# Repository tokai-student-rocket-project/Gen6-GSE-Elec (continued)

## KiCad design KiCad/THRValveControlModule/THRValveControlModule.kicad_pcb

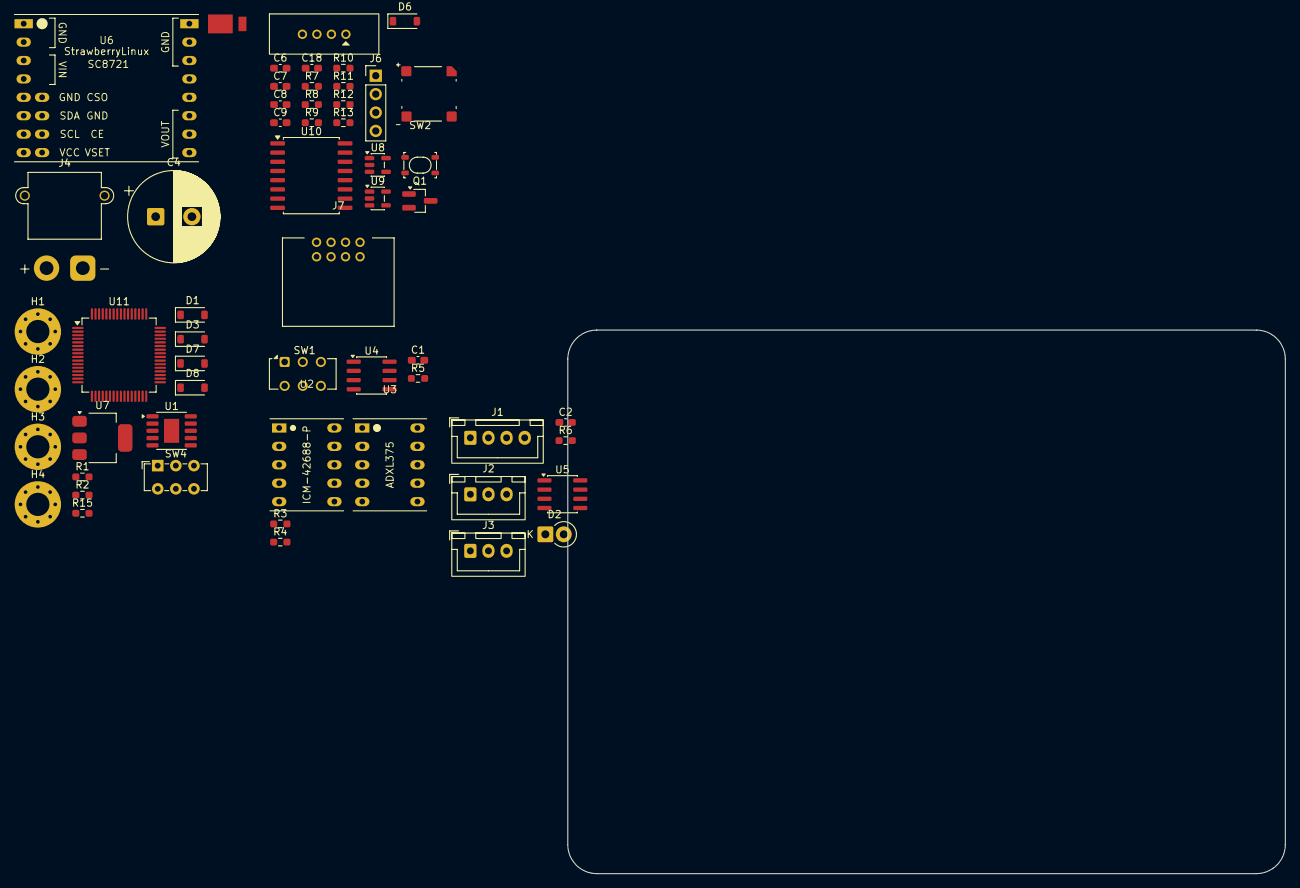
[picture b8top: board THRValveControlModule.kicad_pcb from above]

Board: 2 copper layers, 99.0 x 75.0 mm, 56 parts (0 on the bottom side), 29 nets, no tracks yet.

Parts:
C1, C2, C6, C7, C8, C9: 0.1u; C_0603_1608Metric_Pad1.08x0.95mm_HandSolder
C4: 1000u; CP_Radial_D12.5mm_P5.00mm
C18: 0.1uF; C_0603_1608Metric_Pad1.08x0.95mm_HandSolder
D1, D3, D7, D8: RB160M-30TR; D_SOD-123
D2: P4KE15A; D_DO-41_SOD81_P2.54mm_Vertical_KathodeUp
D5: MA10EB045; MA_DO-221BC
D6: 1N4148W; D_SOD-123
H1, H2, H3, H4: MountingHole; MountingHole_3.2mm_M3_Pad_Via
J1: B4B-XH-A(LF)(SN); JST_XH_B4B-XH-A_1x04_P2.50mm_Vertical
J2, J3: B3B-XH-A(LF)(SN); JST_XH_B3B-XH-A_1x03_P2.50mm_Vertical
J4: XT30PW-M; AMASS_XT30PW-M_1x02_P2.50mm_Horizontal
J5: DF51A-4P-2DSA
J6: SSD1306; PinHeader_1x04_P2.54mm_Vertical
J7: DF51A-8DP-2DS
LS1: UGCT7525AN4
Q1: IRLML6344TRPBFTR; SOT-23_Handsoldering
R1, R2, R7, R8, R10, R11, R12, R13, R15: 10k; R_0603_1608Metric_Pad0.98x0.95mm_HandSolder
R3, R4: 4.7k; R_0603_1608Metric_Pad0.98x0.95mm_HandSolder
R5, R6: 120; R_0603_1608Metric_Pad0.98x0.95mm_HandSolder
R9: 1k; R_0603_1608Metric_Pad0.98x0.95mm_HandSolder
SW1: IS-2235; SW_CK_JS202011CQN_DPDT_Straight
SW2: SKRPACE010
SW4: SW_DPDT_x2; SW_E-Switch_EG1271_SPDT
U1: CH340K; SSOP-10-1EP_3.9x4.9mm_P1mm_EP2.1x3.3mm
U2: ICM-42688; StrawberryLinux_ICM-42688-P
U3: ADXL375; StrawberryLinux_ADXL375
U4: ATA6561; SOIC-8_3.9x4.9mm_P1.27mm
U5: MAX485E; SOIC-8_3.9x4.9mm_P1.27mm
U6: SC8721; StrawberryLinux_SC8721
U7: AZ1117CH-3.3TRG1; SOT-223-3_TabPin2
U8, U9: TC7S14F; SOT-23-5
U10: MB85RQ8MX; SOIC-16W_7.5x10.3mm_P1.27mm
U11: STM32F446RETx; LQFP-64_10x10mm_P0.5mm

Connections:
+3.3V: C7.1, C9.1, C18.1, D3.2 (A), J6.2, R1.1, R2.1, R3.1, R4.1, R7.2, R11.2, R13.1, R15.1, SW4.1 (A), U1.7 (VCC), U1.10 (V3), U2.1 (VDD), U2.2 (VDDIO), U3.9 (VS), U3.10 (VDDI/O), U7.3 (OUT), U8.5 (VCC), U9.5 (VCC), U10.1 (~HOLD(IO3)), U10.2 (VDD), U10.9 (~WP(IO2)), U11.1 (VBAT), U11.13 (VDDA), U11.19 (VDD), U11.32 (VDD), U11.48 (VDD), U11.64 (VDD)
+5V: C1.2, C2.1, D1.2 (A), D6.1 (K), D7.2 (A), LS1.2, U4.3 (VDD), U4.5 (Vio), U5.8 (VCC)
BOOT0: SW4.2 (B), U11.60 (BOOT0)
CAN_H: J7.7, J7.8, R5.1, U4.7 (CANH)
CAN_L: J7.5, J7.6, SW1.1 (A), U4.6 (CANL)
GND: C1.1, C2.2, C4.2, C6.2, C7.2, C8.2, C9.2, C18.2, D2.1 (A1), J1.1, J2.1, J3.1, J4.1, J5.1, J5.3, J6.1, J7.1, J7.2, Q1.2 (S), R10.1, SW2.3 (K), SW2.4 (A), U1.3 (GND), U1.11 (GND), U2.10 (GND), U3.1 (GND), U3.8 (GND), U4.2 (VSS), U4.8 (STBY), U5.5 (GND), U6.1 (GND), U6.2 (GND), U6.5 (GND), U6.10 (GND), U6.18 (GND), U6.19 (GND), U6.20 (GND), U7.2 (GND), U8.3 (GND), U9.3 (GND), U10.10 (VSS), U11.12 (VSSA), U11.18 (VSS), U11.31 (VSS), U11.47 (VSS), U11.63 (VSS)
I2C_SCL: J6.3, R2.2, U6.7 (SCL)
I2C_SDA: J6.4, R1.2, U6.6 (SDA)
unnamed: C6.1, R8.2, U8.2
unnamed: C8.1, R12.2, U9.2
unnamed: D3.1 (K), D7.1 (K), D8.1 (K), U7.1 (IN)
unnamed: D5.2 (A), J4.2
unnamed: D6.2 (A), LS1.1, Q1.3 (D)
unnamed: J5.2, R11.1, R12.1
unnamed: J5.4, R7.1, R8.1
unnamed: Q1.1 (G), R9.1, R10.2
unnamed: R5.2, SW1.2 (B)
Periferal_SwitchA: R13.2, SW2.1, SW2.2
RS485_A: J1.3, R6.1, U5.6 (A)
RS485_B: J1.4, R6.2, U5.7 (B)
RS485_EN: U5.2 (~RE), U5.3 (DE)
SC8721_VIN: D5.1 (K), U6.3 (VIN), U6.4 (VIN)
SC8721_VOUT: C4.1, D2.2 (A2), D8.2 (A), J1.2, J2.2, J3.2, J7.3, J7.4, U6.13 (VOUT), U6.14 (VOUT), U6.15 (VOUT)
SPI_ADXL375_~CS: R4.2, U3.5 (~CS)
SPI_FeRAM0_~CS: R15.2, U10.7 (~CS)
SPI_ICM-42688_~CS: R3.2, U2.6 (~CS)
SPI_SCLK: U2.3 (SCL/SCLK), U3.2 (SCK/SCLK), U10.16 (SCK)
SPI_SDI: U2.4 (SDA/SDI), U3.3 (SDA/SDI/SDIO), U10.15 (SI(IO0))
SPI_SDO: U2.5 (AD0/SDO), U3.4 (SDO/ALT_ADDRESS), U10.8 (SO(IO1))

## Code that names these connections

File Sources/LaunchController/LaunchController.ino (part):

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

namespace power {
  Input killButton(PIN_PJ1, false);
  Output loadSwitch(PIN_PF5);
  Output powerLamp(PIN_PG5);
  Output lowVoltageLamp(PIN_PK7);

  PowerMonitor input(0x40);
  PowerMonitor bus12(0x41);
  Thermistor thermal(PIN_PF4, 10000.0);

  void measureTask();
} // namespace power

namespace control {
  SemiAutoControl safetyArmed(PIN_PC2, false, PIN_PH7);
  SemiAutoControl sequenceStart(PIN_PC3, false, PIN_PG3);
  SemiAutoControl emergencyStop(PIN_PC4, true, PIN_PG4);

  Input confirm1(PIN_PC7, false);
  Input confirm2(PIN_PC6, false);
  Input confirm3(PIN_PC5, false);

  SemiAutoControl shift(PIN_PD4, false, PIN_PH5);
  SemiAutoControl fill(PIN_PD5, false, PIN_PB0);
  SemiAutoControl dump(PIN_PG1, false, PIN_PB5);
  SemiAutoControl oxygen(PIN_PC1, false, PIN_PL4);
  SemiAutoControl igniter(PIN_PD7, false, PIN_PH4);
  SemiAutoControl open(PIN_PD6, false, PIN_PH6);
  SemiAutoControl close(PIN_PG0, false, PIN_PB4);
  SemiAutoControl purge(PIN_PC0, false, PIN_PB6);

  Output shiftFB(PIN_PE3);
  Output fillFB(PIN_PE5);
  Output dumpFB(PIN_PE7);
  Output oxygenFB(PIN_PH3);
  Output igniterFB(PIN_PE2);
  Output openFB(PIN_PE4);
  Output closeFB(PIN_PE6);
  Output purgeFB(PIN_PH2);

  Output statusLamp(PIN_PK4);
  void handleManualTask();

  const String FILL_START = "fill-start";
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} // namespace sequence

namespace n2o {
  TM1637 tm1637(PIN_PK0, PIN_PK1);
} // namespace n2o

namespace error {
  // HACK LEDだけでなく処理もする
  Output statusLamp(PIN_PK6);
} // namespace caution


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    COM_CHECK_S_TO_L
  };

  Output sendEnableControl(PIN_PA2);
  Output accessLamp(PIN_PA4);

  void enableOutput();
  void disableOutput();
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  void onPressureSyncReceived(float pressure);
  void onComCheckReceived();

  Output statusLamp(PIN_PK5);
} // namespace communication


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
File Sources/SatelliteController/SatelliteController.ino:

#include <Arduino.h>
#include <TaskManager.h>
#include <MsgPacketizer.h>
#include "TM1637.hpp"
#include "VESIM10.hpp"
#include "Input.hpp"
#include "Output.hpp"
#include "SemiAutoControl.hpp"
#include "SolenoidMonitor.hpp"
#include "PowerMonitor.hpp"
#include "Thermistor.hpp"


namespace power {
  Input killButton(PIN_PJ1, false);
  Output loadSwitch(PIN_PF5);
  Output powerLamp(PIN_PG5);
  Output lowVoltageLamp(PIN_PK7);

  PowerMonitor input(0x40);
  PowerMonitor bus12(0x41);
  Thermistor thermal(PIN_PF4, 10000.0);

  void measureTask();
} // namespace power

namespace control {
  SemiAutoControl safetyArmed(PIN_PC2, true, PIN_PH7);

  Output shift(PIN_PD4);
  Output fill(PIN_PD5);
  Output dump(PIN_PG1);
  Output oxygen(PIN_PL6);
  Output igniter(PIN_PD7);
  Output open(PIN_PD6);
  Output close(PIN_PG0);
  SemiAutoControl purge(PIN_PC0, true, PIN_PB6);
  // Output purge(PIN_PB6);
  // SemiAutoControl check(PIN_PC0, true, PIN_PB6);

  Output shiftFB(PIN_PH5);
  Output fillFB(PIN_PB0);
  Output dumpFB(PIN_PB5);
  Output oxygenFB(PIN_PL4);
  Output igniterFB(PIN_PH4);
  Output openFB(PIN_PH6);
  Output closeFB(PIN_PB4);
  Output purgeFB(PIN_PH1);

  Output statusLamp(PIN_PK4);
  void handleManualTask();

  void setChristmasTreeStart();
  void setChristmasTreeStop();
} // namespace control

namespace error {
  // HACK LEDだけでなく処理もする
  Output statusLamp(PIN_PK6);
} // namespace caution

namespace solenoid {
  SolenoidMonitor monitor(PIN_PC4);

  void measureTask();
} // namespace solenoid

namespace n2o {
  TM1637 tm1637(PIN_PK0, PIN_PK1);
  VESIM10 vesim10(PIN_PK2, 240.0, 10.0);

  float pressure_MPa = 0.0;

  void measureTask();
} // namespace n2o

namespace umbilical {
  Output flightMode(PIN_PH3);
  Output valveMode(PIN_PH2);
} // namespace umbilical

namespace communication {
  enum class Packet : uint8_t {
    CONTROL_SYNC,
    FEEDBACK_SYNC,
    PRESSURE_SYNC,
    COM_CHECK_L_TO_S,
    COM_CHECK_S_TO_L,
  };

  Output sendEnableControl(PIN_PA2);
  Output accessLamp(PIN_PA4);

  void enableOutput();
  void disableOutput();

  void sendFeedbackSync();
  void sendPressureSync();
  void sendComCheck();
  void onControlSyncReceived(uint8_t state);
  void onComCheckReceived();

  Output statusLamp(PIN_PK5);
} // namespace communication


void setup() {
  power::loadSwitch.on();
  power::powerLamp.on();


  // FT232RL (USB)
  Serial.begin(115200);

  // LTC485 (RS485)
  Serial1.begin(115200);

  // MCP3208 (ADC)
  SPI.begin();
  solenoid::monitor.setDividerResistance(5600, 3300);

  // TM1637 (7SEG)
  n2o::tm1637.initialize();

  // INA219 (Power)
  Wire.begin();
  power::input.begin();
  power::bus12.begin();

  // VESIM10 (N2O Pressure Sensor)
  n2o::vesim10.calibrateBlocking(10);


  Tasks.add(&power::measureTask)->startFps(10);
  Tasks.add(&solenoid::measureTask)->startFps(10);
  Tasks.add(&n2o::measureTask)->startFps(2);
  Tasks.add(&control::handleManualTask)->startFps(50);


  Tasks.add(&communication::sendFeedbackSync)->startFps(10);
  Tasks.add(&communication::sendPressureSync)->startFps(2);
  Tasks.add(&communication::sendComCheck)->startFps(2);
  MsgPacketizer::subscribe(Serial1, static_cast<uint8_t>(communication::Packet::CONTROL_SYNC), &communication::onControlSyncReceived);
  MsgPacketizer::subscribe(Serial1, static_cast<uint8_t>(communication::Packet::COM_CHECK_L_TO_S), &communication::onComCheckReceived);
}


void loop() {
  MsgPacketizer::parse();
  Tasks.update();
}


/// @brief 送信を有効にする
void communication::enableOutput() {
  communication::sendEnableControl.on();
  communication::accessLamp.on();
}


/// @brief 送信を無効にする
void communication::disableOutput() {
  communication::sendEnableControl.off();
  communication::accessLamp.off();
}


void power::measureTask() {
  bool isLowVoltage = power::input.getVoltage_V() < 17.0;
  bool isOverloadedInput = power::input.getAmpere_A() > 3.0;
  bool isOverloadedBus = power::bus12.getAmpere_A() > 3.0;
  bool isOverheated = power::thermal.getTemperature_degC() > 100.0;

  power::lowVoltageLamp.set(isLowVoltage);

  if (isOverloadedInput || isOverloadedBus || isOverheated) {
    // HACK エラー
    error::statusLamp.on();
  }
}


void solenoid::measureTask() {
  // 仮の振る舞い
  bool isArmed = control::safetyArmed.isManualRaised();

  // 正常
  control::shiftFB.set(control::shift.isHigh() && isArmed);
  control::fillFB.set(control::fill.isHigh() && isArmed);
  control::dumpFB.set(control::dump.isHigh() && isArmed);
  control::oxygenFB.set(control::oxygen.isHigh() && isArmed);
  control::igniterFB.set(control::igniter.isHigh() && isArmed);
  control::openFB.set(control::open.isHigh() && isArmed);
  control::closeFB.set(control::close.isHigh() && isArmed);
  control::purgeFB.set(control::purge.isRaised() && isArmed);

  // 故障
  // control::shiftFB.set(control::shift.isHigh() && isArmed ? !control::shiftFB.isHigh() : LOW);
  // control::fillFB.set(control::fill.isHigh() && isArmed ? !control::fillFB.isHigh() : LOW);
  // control::dumpFB.set(control::dump.isHigh() && isArmed ? !control::dumpFB.isHigh() : LOW);
  // control::oxygenFB.set(control::oxygen.isHigh() && isArmed ? !control::oxygenFB.isHigh() : LOW);
  // control::igniterFB.set(control::igniter.isHigh() && isArmed ? !control::igniterFB.isHigh() : LOW);
  // control::openFB.set(control::open.isHigh() && isArmed ? !control::openFB.isHigh() : LOW);
  // control::closeFB.set(control::close.isHigh() && isArmed ? !control::closeFB.isHigh() : LOW);
  // control::purgeFB.set(control::purge.isRaised() && isArmed ? !control::purgeFB.isHigh() : LOW);
}


void n2o::measureTask() {
  float current_mA = n2o::vesim10.getCurrent_mA();

  if (current_mA < 0.1) {
    n2o::tm1637.clearDisplay();
  }
  else {
    n2o::pressure_MPa = n2o::vesim10.getPressure_MPa();
    n2o::tm1637.displayNumber(abs(n2o::pressure_MPa));
  }
}


void communication::sendFeedbackSync() {
  uint8_t state = (control::shiftFB.isHigh() << 0) | (control::fillFB.isHigh() << 1) | (control::dumpFB.isHigh() << 2) | (control::oxygenFB.isHigh() << 3) | (control::igniterFB.isHigh() << 4) | (control::openFB.isHigh() << 5) | (control::closeFB.isHigh() << 6) | (control::purgeFB.isHigh() << 7);

  communication::enableOutput();
  MsgPacketizer::send(Serial1, static_cast<uint8_t>(communication::Packet::FEEDBACK_SYNC), state);
  Serial1.flush();
  communication::disableOutput();
}


void communication::sendPressureSync() {
  communication::enableOutput();
  MsgPacketizer::send(Serial1, static_cast<uint8_t>(communication::Packet::PRESSURE_SYNC), n2o::pressure_MPa);
  Serial1.flush();
  communication::disableOutput();
}


void communication::sendComCheck() {
  communication::enableOutput();
  MsgPacketizer::send(Serial1, static_cast<uint8_t>(communication::Packet::COM_CHECK_S_TO_L));
  Serial1.flush();
  communication::disableOutput();
}


void communication::onControlSyncReceived(uint8_t state) {
  bool isArmed = control::safetyArmed.isManualRaised();

  control::shift.set(state & (1 << 0) && isArmed);
  control::fill.set(state & (1 << 1) && isArmed);
  control::dump.set(state & (1 << 2) && isArmed);
  control::oxygen.set(state & (1 << 3) && isArmed);
  control::igniter.set(state & (1 << 4) && isArmed);
  control::open.set(state & (1 << 5) && isArmed);
  control::close.set(state & (1 << 6) && isArmed);
  control::purge.setAutomatic(state & (1 << 7) && isArmed);

  communication::statusLamp.blink();
}


void communication::onComCheckReceived() {
  communication::statusLamp.blink();
}


void control::handleManualTask() {
  control::statusLamp.blink();

  if (power::killButton.isHigh()) {
    power::loadSwitch.off();
  }

  // セーフティー
  // Armedでなければこの時点で終わり
  control::safetyArmed.setManual();
  if (!control::safetyArmed.isManualRaised()) {
    return;
  }

  // 手動制御
  control::purge.setManual();

  // アンビリカル
  umbilical::flightMode.set(control::igniter.isHigh());
  umbilical::valveMode.set(control::open.isHigh() && !control::close.isHigh());
}

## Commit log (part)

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2023-10-22 説明用写真を追加
2023-10-23 RS485のTX，RXを統合してAccessに変更
2023-10-23 USBのTX，RXを統合してACCESSに変更
2023-10-23 充填確認スイッチ用のコネクタを別に用意
2023-10-23 CAUTIONをERRORに名称変更
2023-10-23 RS485をモジュラージャックからプッシュインコネクタに変更
2023-10-23 ステータスパネルを再設計
2023-10-24 ステータスパネルの裏面に配線を追加
2023-10-24 抵抗値を決定
2023-10-24 ランコンのKiCadプロジェクトをコピーしてサテコンを作成
2023-10-24 音声完成を削除
2023-10-24 手動操作を削除
2023-10-24 残った手動制御を削除
2023-10-24 7セグ用のコネクタを移動
2023-10-24 7セグ用コネクタを6Pから14Pの空いているピンに押し込んだ
2023-10-25 タカチ，IWシリーズのカタログを追加
2023-10-25 タカチ，IW0406Bの図面を追加
2023-10-25 コネクタをまとめた
2023-10-25 タカチ，NKAP915の図面を追加
2023-10-26 刻印を更新
2023-10-26 回路図を整理
2023-10-26 配線を避難させた
2023-10-26 N2O圧力計測回路を追加
2023-10-26 ステータスパネルのコネクタをDF11に変更
2023-11-02 ステータスパネルをビルド
2023-11-02 ランコンをビルド
2023-11-04 サテコンのボード図を作成
2023-11-04 DRCを解決
2023-11-06 GSEのパーツリストを作成
2023-11-07 パーツリストの在庫数を修正
2023-11-08 ヒロセ，LFシリーズのカタログを追加
2023-11-08 NKAP915の製図を追加
2023-11-08 各種写真の整理
2023-11-22 ガーバーファイルを再生成
2023-11-24 抵抗値を修正
2023-11-24 在庫数を更新
2023-11-30 Build3のパーツリストを更新
2023-11-30 Build3に合わせてO2LEDのピンを変更
2023-11-30 スピーカーの音量を最大に変更
2023-11-30 電源制御のみ実装したサテコンのコードを実装
2023-11-30 サテコンの制御スイッチをプルダウンに変更
2023-12-01 サテコンのオープン検知を修正
2023-12-01 シーケンス中にセーフティーが無効になったら穏便ストップをかけるように変更
2023-12-01 アンビリカル出力のテストコードを追加
2023-12-01 TM1637のテストコードを追加
2023-12-01 ストップでフラグを解除するように修正
2023-12-01 エマスト中にも穏便ストップできるように修正
2023-12-01 関数名を間違えていたので修正
2023-12-05 7セグコントローラー用のクラスを自作
2023-12-08 ガーバーファイルを生成
2023-12-27 ランコンからサテコンへの同期を追加
2023-12-27 電磁弁の電圧監視を追加
2023-12-27 コメントを追加
2023-12-27 サンラテ間の同期を追加
2023-12-27 サテコンの自動操作を追加
2023-12-28 サテコンにクリスマスツリーを実装
2023-12-28 クリスマスツリーをシーケンス扱いしないように変更
2023-12-28 名前空間を整理
2023-12-28 電源と温度の監視を追加
2023-12-28 AutoControlを廃止してOutputを使うように変更
2023-12-28 ComCheckを実装
2023-12-28 電磁弁監視を追加
2024-01-22 主電源LEDを追加
2024-02-02 起動音と終了音を追加
2024-04-30 電磁弁の駆動電圧計測を追加
2024-05-03 電源LEDを追加
2024-05-04 サテコンのクリスマスツリーを削除
2024-05-04 FBを一旦点滅させるように変更
2024-05-04 FB_SHIFTの配線を修正
2024-05-04 圧力変換器の電圧表示を追加
2024-05-04 フィードバックを仮で実装
2024-05-04 サテからランのフィードバック同期を追加
2024-05-04 7セグで9が正しく表示されるように修正
2024-05-04 圧力計測の仮の振る舞いを実装
2024-05-04 フィードバックを正常時の振る舞いに変更
2024-05-04 開発用にシーケンス開始ボタンで点火シーケンスを開始できるように変更
2024-05-04 シーケンス進行のフラグを修正
2024-05-04 クリスマスツリーをFBにも適用
2024-05-04 圧力計測は仮で4-20mAの値を表示するように変更
2024-05-10 文法上のミスを修正
2024-05-15 圧力センサの処理をライブラリ化
2024-05-22 電磁弁制御回路を整理
2024-05-23 シルクを修正
2024-05-23 Build4の部品表を作成
2024-05-23 不要なファイルを削除
2024-05-24 ガーバーを出力
2024-05-25 NKAP915に行った追加工の図面を追加
2024-05-25 圧力センサの取り扱い説明書を追加
2024-05-25 NK905Yの完成イメージを追加
2024-05-25 コネクタの写真を追加
2024-11-16 カタログ，データシート，配線図を追加
2024-11-16 分岐アダプターを追加
2024-11-16 PlatformIOの不要なファイルを無視
2024-11-16 開発環境をPlatformIOに移行
2024-11-16 READMEを追加
2024-11-16 ブランチの名前を変更
2024-11-16 回路図とボード図は作ったが必要のなくなったファイルを無視
2024-11-16 分岐アダプターの画像を追加
2024-11-16 Heroを追加
2024-11-17 データフローを更新
2024-11-17 READMEに追記
2024-11-17 マニュアルを追加
2024-11-18 手順書を更新
2024-11-19 🚧 自動シークエンス中にPURGEの動作を追加
2024-11-19 不要なコメントを削除
2024-11-20 ボード図を更新
2024-11-20 こもあの接続を追記
2024-11-20 オートパージ時にdumpがopenになる動作を修正
2024-11-22 timeoutの時間を修正
2024-11-28 受信チェックを工事
2024-11-28 電磁弁断線チェック機能の追加
2024-11-29 故障の状態によってLEDの点灯を変更
2024-11-29 電磁弁の状態をUSBポートから読み出せる機能の追加
2024-11-29 電磁弁のデータシートを追加
2024-11-29 許容電圧を電磁弁の動作許容電圧に更新
2024-12-03 open, close, ignのフィードバックLEDをもとに戻した
2024-12-03 設定値の意味を記述
2024-12-04 いったんコミット
2024-12-04 SafeになったらフィードバックLEDの点灯をOFFにリセット
2024-12-12 配線系統図を追加
2024-12-12 ランチャ周りの設備概要を追加
2024-12-12 配線図を更新
2024-12-18 資料用の写真を追加
2024-12-21 OFF時の閾値を変更
2024-12-21 通信失敗時の処理を更新
2024-12-21 peacefulStop時にpurgeもストップするように変更
2024-12-26 有線で接続されていることを強調
2024-12-26 Taskランプを元に戻した
2024-12-26 通信失敗時の処理をアップデート
2024-12-27 通信失敗時の動作を更新
2024-12-27 READMEを書いていく準備
2024-12-27 名前を変更
2024-12-27 構成一覧を作成
2024-12-27 スペルミスを修正
2024-12-27 READMEを整理
2024-12-27 構成一覧を更新
2024-12-27 仕様を書いていく
2025-01-06 Create LICENSE
2025-01-06 ライセンスを明示
2025-01-15 READMEと仕様を更新
2025-01-15 フォルダ構成の見た目を修正
2025-01-16 ドキュメントの表示位置を修正
2025-01-16 リンクの間違いを修正
2025-01-18 自動シークエンスに関する資料を作成
2025-02-18 LANBOXの図を追加
2025-02-18 点火シークエンスの誤りを修正
2025-03-14 2025年3月8日打上げ実験にて初運用，正常動作
2025-03-27 ギャラリーを追加
2025-03-27 サイズを更新
2025-03-27 リンクのミスを修正
2025-05-20 電気配線図を更新
2025-06-16 イグニッションのタイミング変更（堤先輩）
2025-06-16 髙田 プッシュテスト
2025-06-16 訂正して再プッシュ
2025-06-26 重複していたので修正
2025-06-26 PURGEの時間を変更
2025-07-09 充填確認スイッチの挙動を変更
2025-07-09 GSE周りの配線図を更新
2025-07-22 PlatformIO自動生成ファイルを追跡から削除
2025-07-22 KiCAD9.0に対応したはず
2025-07-22 圧力センサを校正し書き込み
2025-07-22 足りなかったライブラリを追加
2025-11-19 伊阪 プッシュテスト
2026-01-23 .pioを無視するように変更
2026-01-23 .pio 以下を無視するように変更
2026-01-23 .gitignore が反映されなかったためコミット
2026-01-23 .gitignore が反映されなかったので修正
2026-01-23 燃焼実験専用のバルブコントロールモジュールを作成
2026-01-23 THR-E810L で点火した時の設定をコメントアウト
2026-01-23 複数のライブラリを追加
2026-01-24 11~18ピンのはんだ不良無し
2026-01-24 設定ファイルを更新
2026-01-28 SPIモード3にソフトウェア的に対応
2026-01-28 ライブラリを追加
2026-01-28 燃焼実験用バルブコントロール基板を追加
2026-01-28 環境を更新
2026-02-16 関数を追加
2026-02-16 ファイルを整理
2026-02-16 校正シートを作成
2026-02-16 機能を追加
2026-02-16 遠隔でセンサーを校正・監視できる仕組みを追加
2026-02-16 HSV機能を追加
2026-02-16 ライブラリを作成
2026-02-16 ライブラリを移植
2026-02-16 燃焼実験用モジュールを作成中
2026-02-16 とりあえずプッシュ
2026-02-16 実験したデータを追加
2026-02-17 バックグラウンドでN2O圧力を計測するように変更
2026-02-17 通信が機能しないため一回プッシュ
2026-02-18 通信エラー時はエラーランプがONになるように修正
2026-02-18 余計な記載を削除
2026-02-18 INPUTライブラリを修正
2026-02-18 TaskManager と MsgPacketizer の設定値を変更
2026-02-18 通信・タスク管理ライブラリのドキュメントを作成
2026-02-18 データシートを追加
2026-02-18 特に変更無し
2026-02-18 VESIM10 のマニュアルを更新
2026-02-18 READMEを更新
2026-02-18 LEDの点滅を人間が確認可能な範囲へ変更
2026-02-18 関数の追加
2026-02-20 GUIを作成
2026-02-21 電源再投入後，ある圧力範囲を超えていたら，ゼロ点校正を行わないように変更
2026-02-21 ゼロ点校正実行条件を追加
2026-02-21 校正をした．傾きは0.5777．書き込み済み
2026-04-09 センサー周りのコードを変更
2026-04-09 Build-1 は失敗
2026-04-09 KiCad9.0に対応
2026-04-09 LaunchController2.0を開発中
2026-04-09 絶縁RS485
2026-04-09 マイコン
2026-04-09 シリアル変換
2026-04-09 テストしたデータを追加
2026-04-09 STM32でテスト環境を構築
2026-04-09 絶縁RS485モジュールを試した
2026-04-10 テストしたログを追加
2026-04-10 gifを追加
2026-04-10 コメントを変更
2026-04-11 4層基板から2層基板へ仕様変更
2026-04-11 Build-1いったん完成
2026-04-11 SatelliteController2.0の設計開始
2026-04-29 スイッチのデータシートを追加
2026-04-29 RS485通信テストした
2026-04-29 Build-1発行＆発注
2026-04-29 特に変更はしてない．閲覧しただけ
2026-04-29 QRコードを追加．シルクプリントに使える．
2026-04-29 進捗40%くらい
2026-04-29 SatelliteNode-Switch Build-1発行
2026-05-01 6軸加速度センサーから値の読み出しに成功
2026-05-04 USB＋，USB－の配線を修正
2026-05-05 はんだづけに使った資料を追加
2026-05-05 はんだ付けに使う資料を追加
2026-05-05 EEPROMのライブラリを作成中
2026-05-05 teleplot用の設定を追記
2026-05-05 共通ライブラリの設定を追加
2026-05-23 ランチコントローラー2.0のコード製作開始
2026-05-23 サテライトコントローラー2.0のコード製作開始
2026-05-23 メモリのライブラリを作成
2026-05-24 構成図を追加
2026-05-24 パーツの写真を追加
2026-05-24 安全審査用の図を追加
2026-05-24 SatelliteNode Build-1を発行
2026-05-24 ADS1115のライブラリを作成
2026-05-24 ADS1115から得た電圧値を計算に使用するように変更
2026-05-24 ピン番号を整えた
2026-05-24 SatelliteController2.0の回路とソフトを対応させた
2026-05-24 サテライトコントローラー2,0専用ライブラリを追加
2026-05-24 サテライトコントローラー2.0専用として追加
2026-05-28 燃焼実験成功
2026-05-30 特に変更なし
2026-05-30 Seeed RA4M1用
2026-05-30 サテライトノードのプログラムを追加
2026-05-30 THR-820Nの実験を実施．不点火
2026-05-30 環境を構築
2026-06-06 LEDの光り方を数種類追加
2026-06-06 Build-2 を発行
2026-06-06 SatelliteNodeと通信できるように変更
2026-06-06 Neopixelを使用可能に リミットスイッチが押された時の動作を追加
2026-06-06 O2の電磁弁を更新予定 データシートを追加
2026-06-06 通信の周波数を変更
2026-06-06 RS485の通信エラーを解消
2026-06-06 Neopixelの光り方の更新を制限
2026-06-07 通信方式をポーリング方式に変更
2026-06-10 FILL弁の仕様を戻した
2026-06-10 環境を変更
2026-06-10 フリーズせずに動作していそう
2026-06-19 ソレノイドモニターを更新
